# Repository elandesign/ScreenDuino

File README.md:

# ScreenDuino
General purpose Arduino pro mini clone w/PCD8544 screen and 4 x buttons

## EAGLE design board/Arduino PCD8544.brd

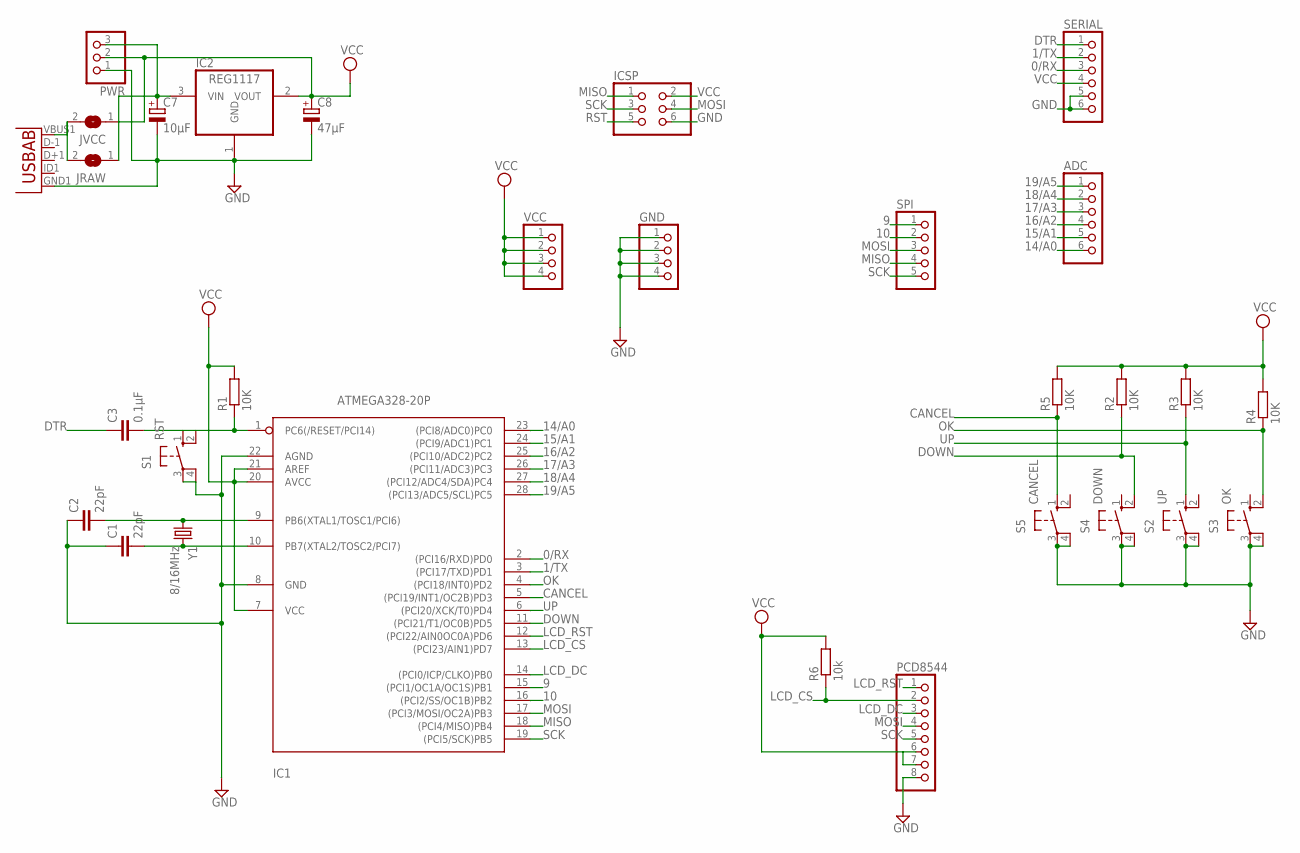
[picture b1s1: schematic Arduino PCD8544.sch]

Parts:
ADC: PINHD-1X6; 1X06
C1, C2: 22pF; C0805
C3: 0.1µF; C0805
C7: 10µF; E2,5-5
C8: 47µF; E2,5-5
GND: PINHD-1X4; 1X04
IC1: ATMEGA328-20P; DIL28-3
IC2: REG1117; SOT223
ICSP: PINHD-2X3; 2X03
JRAW: SJ
JVCC: SJ
PCD8544: PINHD-1X8; 1X08
PWR: PINHD-1X3; 1X03
R1, R2, R3, R4, R5: 10K; R0805
R6: 10k; R0805
S1: RST; B3F-10XX
S2: UP; B3F-10XX
S3: OK; B3F-10XX
S4: DOWN; B3F-10XX
S5: CANCEL; B3F-10XX
SERIAL: PINHD-1X6; 1X06
SPI: PINHD-1X5; 1X05
U1: USB""; USB-MICRO-SMD
VCC: PINHD-1X4; 1X04
Y1: 8/16MHz; HC49US

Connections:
0/RX: IC1.2 ((PCI16/RXD)PD0), SERIAL.3
1/TX: IC1.3 ((PCI17/TXD)PD1), SERIAL.2
9: IC1.15 ((PCI1/OC1A/OC1S)PB1), SPI.1
10: IC1.16 ((PCI2/SS/OC1B)PB2), SPI.2
14/A0: ADC.6, IC1.23 ((PCI8/ADC0)PC0)
15/A1: ADC.5, IC1.24 ((PCI9/ADC1)PC1)
16/A2: ADC.4, IC1.25 ((PCI10/ADC2)PC2)
17/A3: ADC.3, IC1.26 ((PCI11/ADC3)PC3)
18/A4: ADC.2, IC1.27 ((PCI12/ADC4/SDA)PC4)
19/A5: ADC.1, IC1.28 ((PCI13/ADC5/SCL)PC5)
CANCEL: IC1.5 ((PCI19/INT1/OC2B)PD3), R5.1, S5.1 (S)
DOWN: IC1.11 ((PCI21/T1/OC0B)PD5), R2.1, S4.2 (S1)
DTR: C3.1, SERIAL.1
GND: C1.1, C2.1, C7.-, C8.-, GND.1, GND.2, GND.3, GND.4, IC1.8 (GND), IC1.22 (AGND), IC2.1 (GND), ICSP.6, PCD8544.8, PWR.1, S1.3, S1.4 (P1), S2.3, S2.4 (P1), S3.3, S3.4 (P1), S4.3, S4.4 (P1), S5.3, S5.4 (P1), SERIAL.5, SERIAL.6, U1.GND1 (GND)
LCD_CS: IC1.13 ((PCI23/AIN1)PD7), PCD8544.2, R6.1
LCD_DC: IC1.14 ((PCI0/ICP/CLKO)PB0), PCD8544.3
LCD_RST: IC1.12 ((PCI22/AIN0OC0A)PD6), PCD8544.1
MISO: IC1.18 ((PCI4/MISO)PB4), ICSP.1, SPI.4
MOSI: IC1.17 ((PCI3/MOSI/OC2A)PB3), ICSP.4, PCD8544.4, SPI.3
unnamed: JRAW.2, JVCC.2, U1.VBUS1 (VBUS)
OK: IC1.4 ((PCI18/INT0)PD2), R4.1, S3.2 (S1)
RAW: C7.+, IC2.3 (VIN), JRAW.1, PWR.3
RST: C3.2, IC1.1 (PC6(/RESET/PCI14)), ICSP.5, R1.1, S1.1 (S), S1.2 (S1)
SCK: IC1.19 ((PCI5/SCK)PB5), ICSP.3, PCD8544.5, SPI.5
UP: IC1.6 ((PCI20/XCK/T0)PD4), R3.1, S2.1 (S)
VCC: C8.+, IC1.7 (VCC), IC1.20 (AVCC), IC1.21 (AREF), IC2.2 (VOUT), ICSP.2, JVCC.1, PCD8544.6, PCD8544.7, PWR.2, R1.2, R2.2, R3.2, R4.2, R5.2, R6.2, SERIAL.4, VCC.1, VCC.2, VCC.3, VCC.4
XTAL1: C2.2, IC1.9 (PB6(XTAL1/TOSC1/PCI6)), Y1.1
XTAL2: C1.2, IC1.10 (PB7(XTAL2/TOSC2/PCI7)), Y1.2

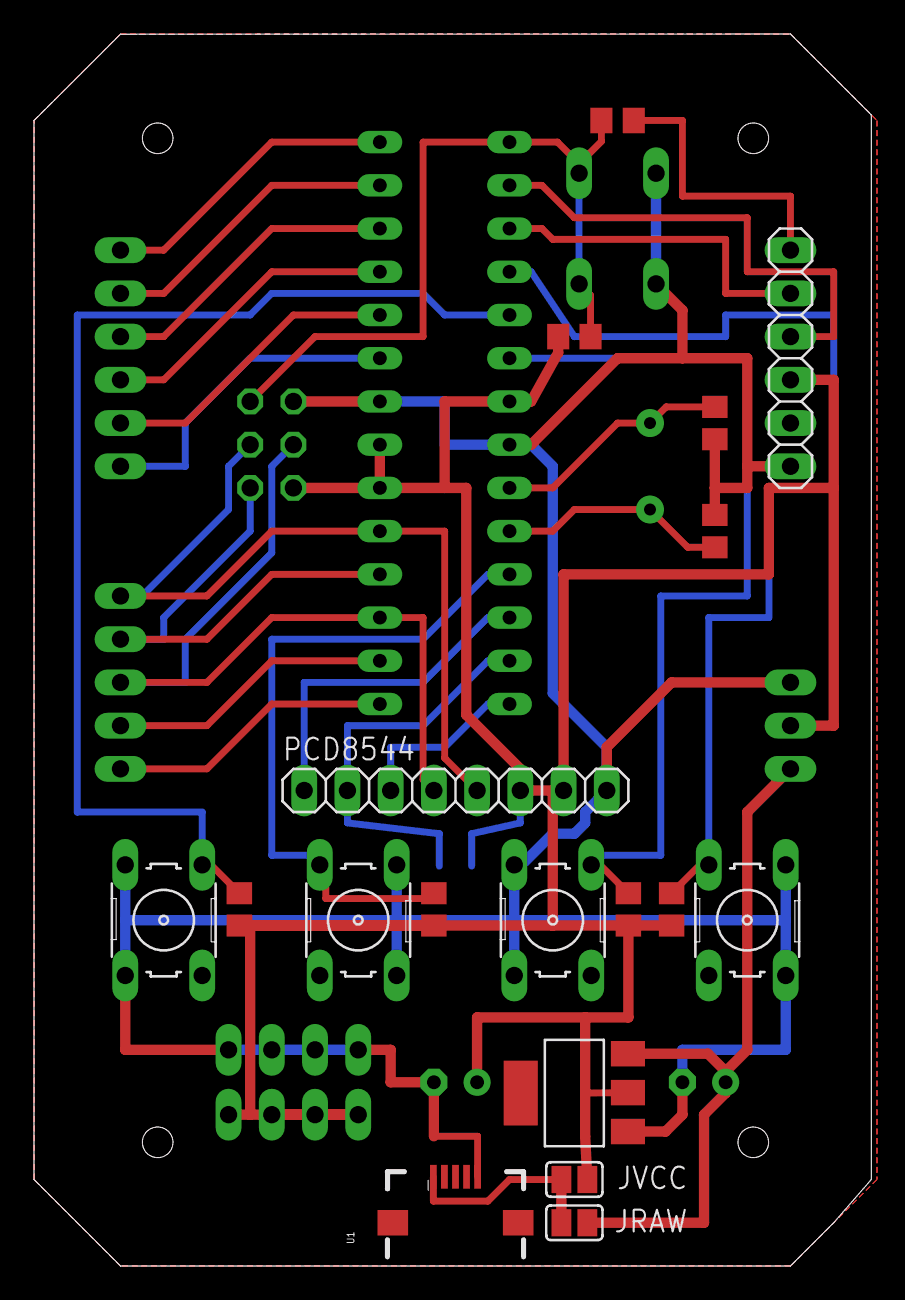
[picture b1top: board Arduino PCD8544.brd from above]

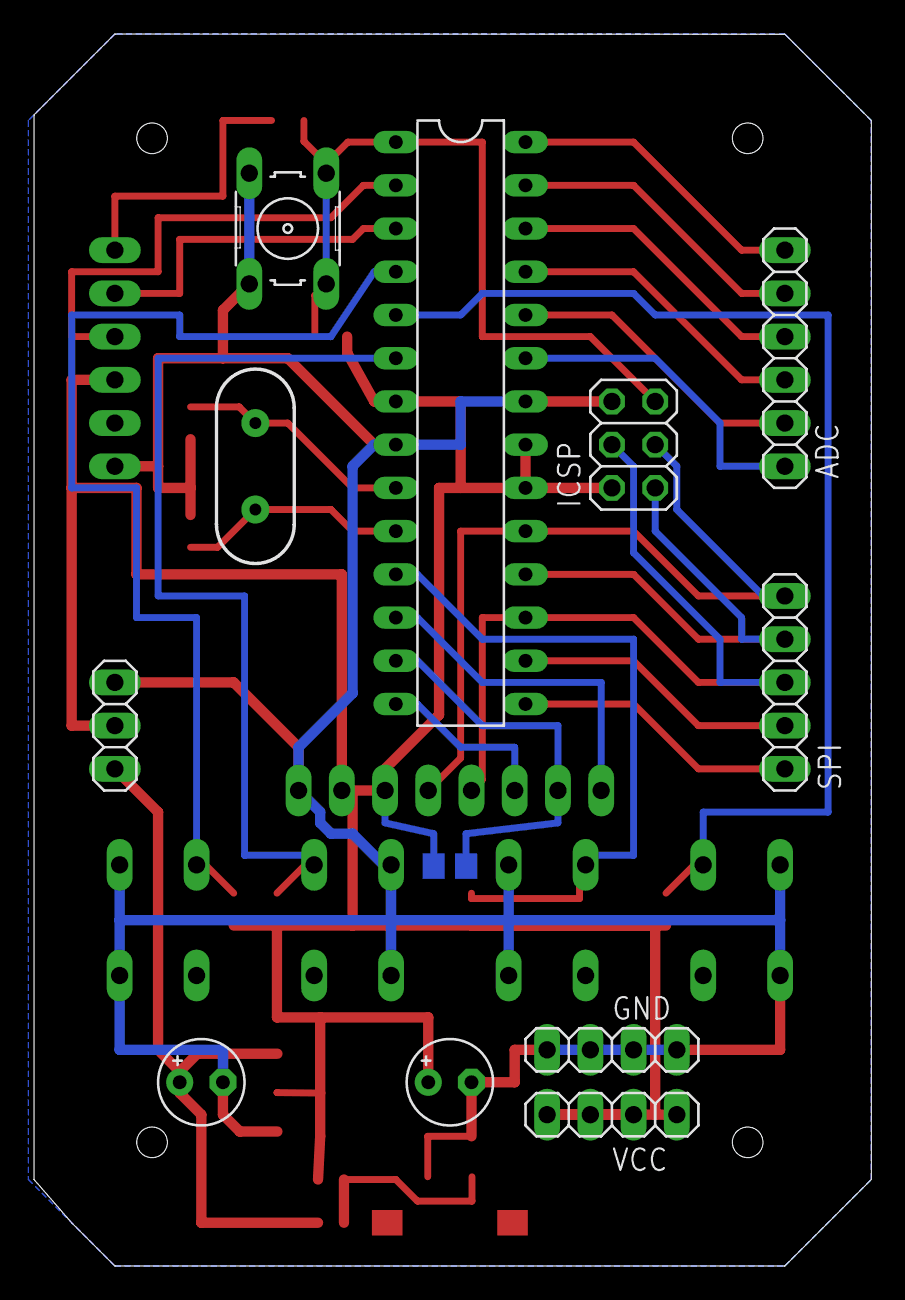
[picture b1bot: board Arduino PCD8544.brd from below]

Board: 2 copper layers, 49.2 x 72.4 mm, 30 parts (12 on the bottom side), 28 nets.

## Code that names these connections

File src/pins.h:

#ifndef PINS_H
#define PINS_H

#define PIN_LCD_RST 6 // PD6
#define PIN_LCD_CS 7 // PD7
#define PIN_LCD_DC 8 // PB0

#define PIN_OK 2 // PD2 PCINT18
#define PIN_CANCEL 3 // PD3 PCINT19
#define PIN_UP 4 // PD4 PCINT20
#define PIN_DOWN 5 // PD5 PCINT21

#define PIN_SCLK 13
#define PIN_MOSI 11

#endif

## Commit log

2017-02-03 ScreenDuino - Arduino Pro Mini clone with PCD8544 display
2017-02-04 Use the correct pin for MOSI
2017-02-04 Use software debounce on input buttons
2017-02-04 Configure for 8MHz crystal
2017-02-04 Add Eagle board schematic
2017-02-04 Add README.md
2017-02-04 Updated board
    * Moved push button and power positions
    * Moved µUSB to bottom centre of board
    * Added mounting holes to suit https://evatron.com/enclosures/oval-enclosures/sb107g/

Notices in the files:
parts and their libraries:
SparkFun-FreqCtrl: Licensing: Creative Commons ShareAlike 4.0 International - https://creativecommons.org/licenses/by-sa/4.0
